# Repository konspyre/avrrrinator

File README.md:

# avrrrinator

These are the Eagle source files for the Avrrrinator, a Bus Pirate 3 to AVR ISP adapter. Instead of running a rats nest of wiring to the Bus Pirate for programming, these adapters break everything out into the standard 6-pin ISP connector available on many boards. 

A cable connection is all that is required to begin programming your board using the Bus Pirate and avrdude.

### Which should I choose?

#### [Avrrrinator Rev. A](hardware/revA)

Straight Bus Pirate to AVR breakout with 5v/3.3v selection. No logic level
translation. Simple and works.

#### [Avrrrinator Rev. B](hardware/revB)

Revision B isn't a program-many-AVRs-at-once board\*, but lets you connect more than one AVR for individual programming. This is great for prototyping and flipping different bits on two identical circuits (low power projects, debugging, etc). 

The Eagle files are available for Rev B. Not much will change since this ended up being more of a toy/experimental project than anything else. It works though!

\* Saying parallel would be confusing since old-school parallel port AVR programmers are out there (and with many likely still in use).

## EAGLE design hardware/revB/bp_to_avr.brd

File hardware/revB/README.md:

# Avrrrinator Rev. B

### Fabrication (OSHPark shared project)

[Shared at OSHPark](https://oshpark.com/shared_projects/C2GnBJb3)

### Bill of Materials for Revision B
| Quantity | Description | Part number | Board Placement |
| -------- | ----------- | ----------- | --------------- |
| 2        | 6 pin AVR ISP header | [Mouser: 517-9612066404AR](http://www.mouser.com/Search/Refine.aspx?Keyword=517-9612066404AR) | ISP CS and ISP AUX (6-pin through-hole footprints) |
| 2        | 0.1"/2.54mm breakaway header (2 pins needed for each) | 36-pin header: [Mouser: 649-68004-236](http://www.mouser.com/Search/Refine.aspx?Keyword=649-68004-236) | AVR CS PWR/AUX PWR pins (two pins each) |
| 2        | Jumper/Power coupler | [Mouser: 151-8033-E](http://www.mouser.com/Search/Refine.aspx?Keyword=151-8033-E) (Red) / [Mouser: 151-8031-E](http://www.mouser.com/Search/Refine.aspx?Keyword=151-8031-E) (Blue) | Jumpers on two-pin CS/AUX power normally placed to close |
| 1        | 10 pin PCB to Bus Pirate 3 female connector | [Mouser: 517-8510-4500PL](http://www.mouser.com/Search/Refine.aspx?Keyword=517-8510-4500PL) | Bus Pirate v3 header (bottom side with keyed slot matching outline) | 
| 2        | AVR ISP cable (6-pin to 6-pin f/f)\* | [Adafruit: PID 371](http://www.adafruit.com/products/371) | N/A |
| 2        | 0603 imperial 0.1µF capacitors | [Mouser: VJ0603Y104JXJPW1BC](http://www.mouser.com/Search/Refine.aspx?Keyword=VJ0603Y104JXJPW1BC) | C1 and C2 |
| 2        | 74HC125 buffers | [Mouser: SN74HC125PWR](http://www.mouser.com/Search/Refine.aspx?Keyword=SN74HC125PWR) | IC1 and IC2 - Match silkscreen circle orientor with IC's |
| 8        | 0603 imperial 10k ohm resistors | [Mouser: CR0603-JW-103GLF](http://www.mouser.com/Search/Refine.aspx?Keyword=CR0603-JW-103GLF) | R1, R2, R3, R4, R5, R6, R7, R8 (or R1-R8) |
| 2        | Surface mount power selection switch | [Mouser](http://www.mouser.com/Search/Refine.aspx?Keyword=PCM12SMTR)/[Digikey](http://www.digikey.com/product-detail/en/PCM12SMTR/401-2016-1-ND/)/[Newark](http://www.newark.com/c-k-components/pcm12smtr/switch-slide-spdt-300ma-through/dp/28C3147): PCM12SMTR | Top and bottom switches (they should fit into the non-plated drills and be somewhat flush with the board | 

* Colorful (and somewhat odd) alternative at [Digikey P/N: SAM8734-ND](http://www.digikey.com/product-detail/en/IDSD-03-D-06.00-T/SAM8734-ND/3476372). Mouser used to sell a proper 6-pin IDC cable, but they don't anymore (or it is really well hidden).

### Alternative connector for Bus Pirate to Avrrrinator Rev. B

Exchanging the Bus Pirate <-> Avrrrinator connector for these two items allows the Avrrrinator PCB to be located further away from the Bus Pirate. This was the method used in early prototypes (it isn't recommended since things just end up flopping everywhere).

| Quantity | Description | Part number |
| -------- | ----------- | ----------- |
| 1        | 10-pin IDC cable | [Adafruit: 370](adafru.it/370) |
| 1        | 10-pin box connector | [Mouser: 538-90130-1110](http://www.mouser.com/Search/Refine.aspx?Keyword=5538-90130-1110) |

### More information/boring blog post

[http://open.konspyre.org/avrb](http://open.konspyre.org/avrb)

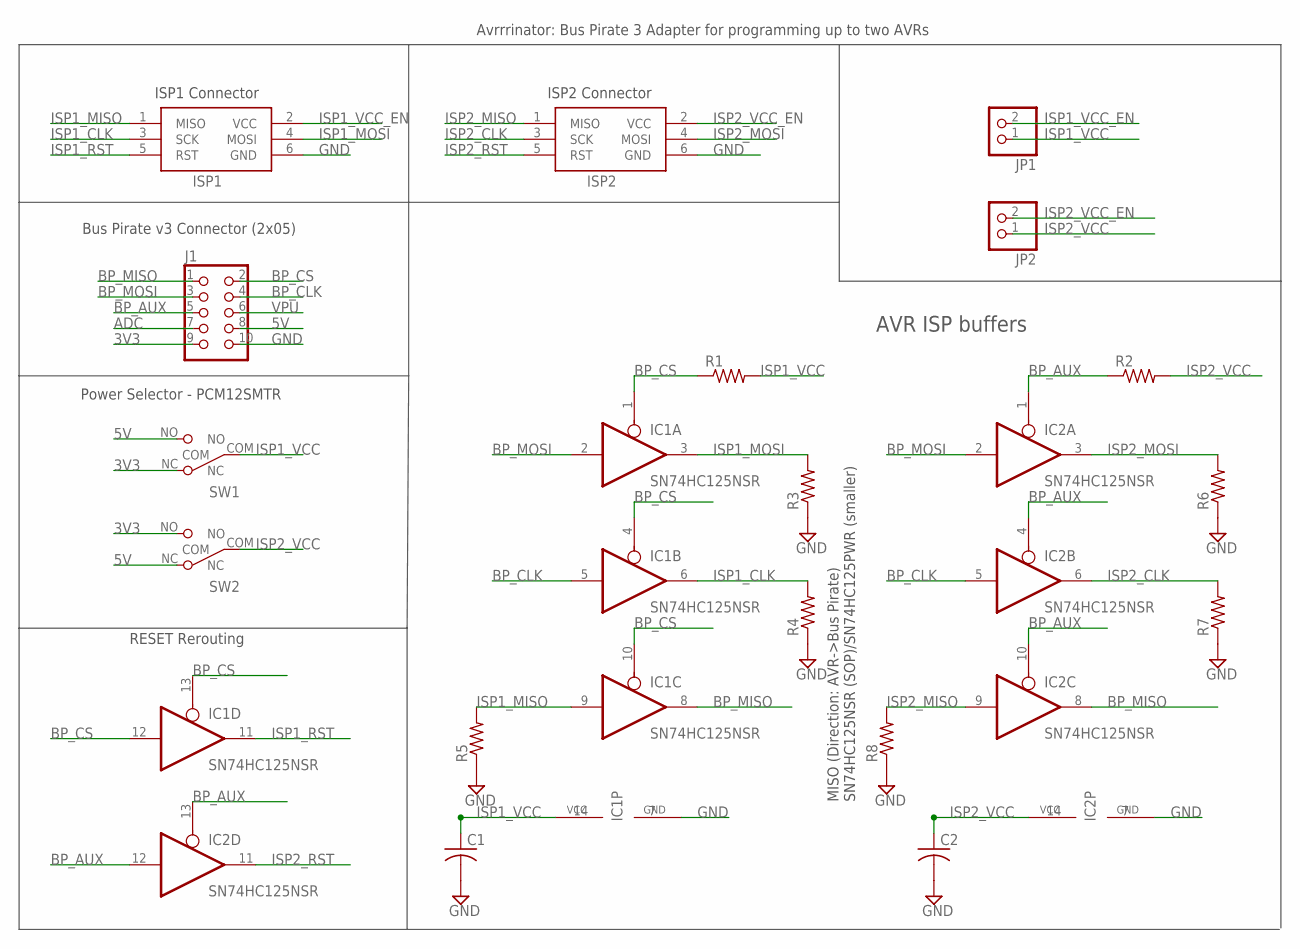
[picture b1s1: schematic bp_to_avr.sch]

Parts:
C1, C2: C-USC0603; C0603
IC1, IC2: SN74HC125NSR; AVRRRINATOR-PWR
ISP1, ISP2: AVRRRINATOR-AVRISP-6PIN-6; AVRRRINATOR-AVRISP-6PIN
J1: CON_HEADER_2X05-PTH+SHROUDED_B; PINSHRD_PTH_2X05B
JP1, JP2: HEADER-1X2ROUND; 1X02_ROUND
R1, R2, R3, R4, R5, R6, R7, R8: R-US_R0603; R0603
SW1, SW2: SW_SLIDE; SLIDE_SWITCH_SMD

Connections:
3V3: J1.9, SW1.NC, SW2.NO
5V: J1.8, SW1.NO, SW2.NC
ADC: J1.7
BP_AUX: IC2.1 (OE), IC2.4 (OE), IC2.10 (OE), IC2.12 (I), IC2.13 (OE), J1.5, R2.1
BP_CLK: IC1.5 (I), IC2.5 (I), J1.4
BP_CS: IC1.1 (OE), IC1.4 (OE), IC1.10 (OE), IC1.12 (I), IC1.13 (OE), J1.2, R1.1
BP_MISO: IC1.8 (O), IC2.8 (O), J1.1
BP_MOSI: IC1.2 (I), IC2.2 (I), J1.3
GND: C1.2, C2.2, IC1.7 (GND), IC2.7 (GND), ISP1.6 (GND), ISP2.6 (GND), J1.10, R3.1, R4.1, R5.1, R6.1, R7.1, R8.1
ISP1_CLK: IC1.6 (O), ISP1.3 (SCK), R4.2
ISP1_MISO: IC1.9 (I), ISP1.1 (MISO), R5.2
ISP1_MOSI: IC1.3 (O), ISP1.4 (MOSI), R3.2
ISP1_RST: IC1.11 (O), ISP1.5 (RST)
ISP1_VCC: C1.1, IC1.14 (VCC), JP1.1, R1.2, SW1.COM
ISP1_VCC_EN: ISP1.2 (VCC), JP1.2
ISP2_CLK: IC2.6 (O), ISP2.3 (SCK), R7.2
ISP2_MISO: IC2.9 (I), ISP2.1 (MISO), R8.2
ISP2_MOSI: IC2.3 (O), ISP2.4 (MOSI), R6.2
ISP2_RST: IC2.11 (O), ISP2.5 (RST)
ISP2_VCC: C2.1, IC2.14 (VCC), JP2.1, R2.2, SW2.COM
ISP2_VCC_EN: ISP2.2 (VCC), JP2.2
VPU: J1.6

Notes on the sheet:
Avrrrinator: Bus Pirate 3 Adapter for programming up to two AVRs
Power Selector - PCM12SMTR
Bus Pirate v3 Connector (2x05)
AVR ISP buffers
MISO (Direction: AVR->Bus Pirate) SN74HC125NSR (SOP)/SN74HC125PWR (smaller)
ISP1 Connector
ISP2 Connector
RESET Rerouting

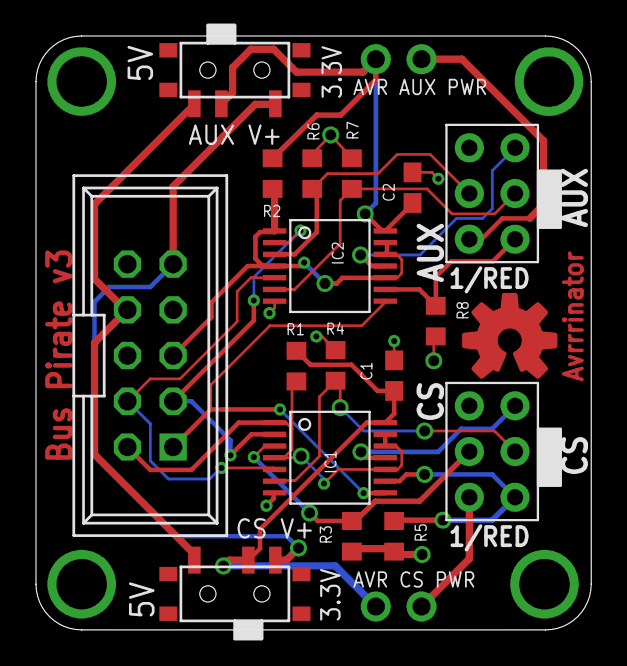
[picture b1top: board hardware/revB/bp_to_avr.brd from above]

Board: 2 copper layers, 30.8 x 33.0 mm, 20 parts (0 on the bottom side), 20 nets.

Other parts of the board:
U$1: ADAFRUIT_OSHWLOGO_TOP_0.2_NO_MASK

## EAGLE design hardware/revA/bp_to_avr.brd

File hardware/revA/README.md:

# Avrrrinator Rev. A

This is a single-ended AVR ISP breakout for use with the Bus Pirate v3. It connects directly to the Bus Pirate via a keyed header.

There is a voltage selection jumper that allows simple switching between the 5v and 3.3v rails provided by the Bus Pirate. Note that while this board allows voltage selection between the Bus Pirate's provided power
rails (5V or 3.3V) that the logic levels are fixed at 3.3v during programming.

## Use

1. Install avrdude

2. Install/plug in your Bus Pirate 3 and make sure that it works on your system. [Bus Pirate AVR programming guide](http://dangerousprototypes.com/docs/Bus_Pirate_AVR_Programming)

3. Plug in all cables, attach the Avrrrinator PCB to the Bus Pirate (note orientation of all cabling before applying power). 
 
4. Set the voltage jumper to your desired level.

5. Write to your AVR breakouts with the following: `avrdude -v -p attiny4313 -c buspirate -P /dev/ttyUSB0 -U flash:w:blinky4313.hex`

Replace: `attiny4313`, `/dev/ttyUSB0`, and `blinky4313.hex` with values from your own environment. 

### Bill of Materials for Revision A
| Quantity | Description | Part number |
| -------- | ----------- | ------ |
| 1        | 6 pin AVR ISP header | [Mouser: 517-9612066404AR](http://www.mouser.com/Search/Refine.aspx?Keyword=517-9612066404AR) |
| 1        | 3 pin breakaway header | 36-pin header: [Mouser: 649-68004-236](http://www.mouser.com/Search/Refine.aspx?Keyword=649-68004-236) / Alternative (3-pin, untested!): [Mouser: 571-1031853](http://www.mouser.com/Search/Refine.aspx?Keyword=571-1031853) |
| 1        | Jumper/Power selector | [Mouser: 151-8033-E](http://www.mouser.com/Search/Refine.aspx?Keyword=151-8033-E) (Red) / [Mouser: 151-8031-E](http://www.mouser.com/Search/Refine.aspx?Keyword=151-8031-E) (Blue) |
| 1 	   | 10 pin PCB to Bus Pirate 3 female connector | [Mouser: 517-8510-4500PL](http://www.mouser.com/Search/Refine.aspx?Keyword=517-8510-4500PL)
| 1 	   | AVR ISP cable (6-pin to 6-pin f/f)\* | [Adafruit: PID 371](http://www.adafruit.com/products/371)

* Colorful (and somewhat odd) alternative at [Digikey P/N: SAM8734-ND](http://www.digikey.com/product-detail/en/IDSD-03-D-06.00-T/SAM8734-ND/3476372). Mouser used to sell a proper 6-pin IDC cable, but they don't anymore (or it is really well hidden).

## Fabrication

**Please note**: Due to the extra I/O pins, this breakout is not readily compatible with a **v4** Bus Pirate.

Get these made at OSHPark by [clicking here](https://oshpark.com/shared_projects/tvIUA78A).

## Assembly

1. Snap 3 pins off of the breakaway header and solder it into the voltage selection area.
2. Solder in the 6-pin ISP header
3. Solder in the Bus Pirate mating header (10 pins).

#### Assembly notes

Most of the difficulty in assembling this board is soldering the 10-pin mating header. There is an alignment line silkscreened on the back
to assist with getting it straight (and in the right orientation). To get a decent result, try soldering one corner pin in, aligning it with 
the silk, and then tacking in an opposite corner.
 
The other headers (power select, 6-pin ISP header) can also be placed with decent precision using this method.

## Todo

Complete assembly writeup (for the brave, just slot in all the components where they fit).

## Notable changes

Revision A2: Silkscreen updates (mostly written on the mask layer), along with BOM change to a direct mounting header.

Revision A1: Initial release. [Previous documentation and BOM](http://open.konspyre.org/blog/2013/01/23/the-avrrrinator-revision-a/).

## Licensing

CC0 Public Domain

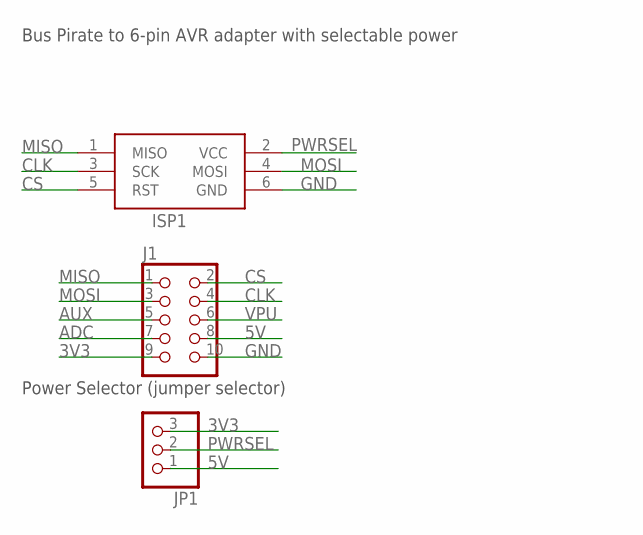
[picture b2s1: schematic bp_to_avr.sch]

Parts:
ISP1: AVRISP-6; AVRISP
J1: CON_HEADER_2X05-PTH+SHROUDED_B; PINSHRD_PTH_2X05B
JP1: PINHD-1X3; 1X03

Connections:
3V3: J1.9, JP1.3
5V: J1.8, JP1.1
ADC: J1.7
AUX: J1.5
CLK: ISP1.3 (SCK), J1.4
CS: ISP1.5 (RST), J1.2
GND: ISP1.6 (GND), J1.10
MISO: ISP1.1 (MISO), J1.1
MOSI: ISP1.4 (MOSI), J1.3
PWRSEL: ISP1.2 (VCC), JP1.2
VPU: J1.6

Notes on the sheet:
Bus Pirate to 6-pin AVR adapter with selectable power
Power Selector (jumper selector)

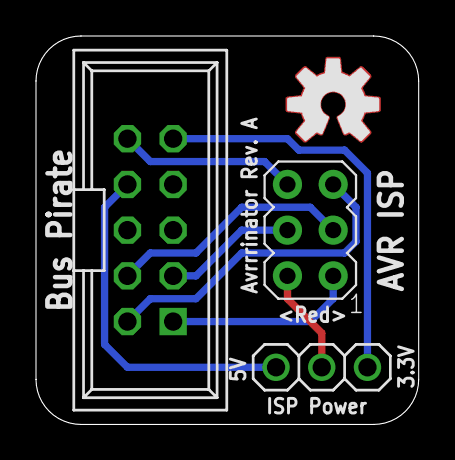
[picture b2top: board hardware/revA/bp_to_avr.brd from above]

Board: 2 copper layers, 21.3 x 21.6 mm, 5 parts (0 on the bottom side), 8 nets.

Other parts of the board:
U$1: OSHWLOGO_TOP_0.2
U$2: OSHW-LOGO-M

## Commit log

2013-01-23 Add board layout & schematic files
2013-01-23 Add board preview images
    These were generated by OSHPark's board preview system.
2013-04-17 Include a README w/docs since the URL at the top may change
2014-03-11 Rename current revision files for historical continuity
2014-03-11 Avrrrinator Rev. A cosmetic/BOM changes
    - Align OSHW logo w/PCB use direction + no mask
    - Has bottom alignment silk for bus pirate header underneath
    - Poly pour + mask text
2014-03-11 Bill of Materials + README for Avrrrinator Rev. A
2014-03-11 Update main README to separate Avrrrinator revisions
2014-03-11 Remove obsolete Rev A PCB previews
2014-03-11 Avrrrinator Rev. A: Add link for fabrication + license
2014-03-11 revA: Add more steps to usage (aka profit)
    Also add a TODO section that may or may not get done, depending on photography skills and available sunlight.
2014-03-11 revA: Add assembly steps
2014-03-12 Add Avrrrinator Rev A2 image
2014-03-12 Add board picture
2014-03-12 Bus Pirate v4 note
2014-03-12 avrA: Add blue pull jumper
2014-03-20 Add link to revA from main readme
2014-03-20 Add rev A image
2014-03-20 Remove spurious url from readme
2014-03-22 Deploy a surprise preview.
2014-03-22 README: Fix a typo
2014-03-22 README: avrB notes
2014-04-07 avrB detail
2014-04-20 Add revB eagle board/schematic files
    Licensing: Creative Commons Attribution, Share-Alike license
2014-04-21 Release Rev B
2014-04-21 Introductory notes
2014-05-02 Move usage to the top of the page
2014-05-04 Bill of Materials
2014-05-04 Add placement locations
2014-05-04 More fixes to BOM
2014-05-15 Link through from main images
2014-05-18 avrb: Update descriptions to be more.. descriptive
2014-05-19 Update for release (+shared project, +blag)

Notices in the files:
parts and their libraries:
SparkFun-Aesthetics: Licensing: CC v3.0 Share-Alike You are welcome to use this library for commercial purposes.
